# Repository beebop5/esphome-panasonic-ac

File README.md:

# ESPHome Panasonic AC Component (WLAN + CNT)

A custom ESPHome component for controlling Panasonic air conditioning units via UART communication through either:
- **WLAN interface (CN-WLAN port)** (DNSK-P11 compatible)
- **CNT interface (CN-CNT port)** (CZ-TACG1 compatible)

This provides a local-control alternative to Panasonic adapters, without Comfort Cloud.

## Features

* 🌡️ **Climate Control**: Full temperature control with heating, cooling, dry, and fan modes
* 🌪️ **Fan Control**: Automatic and manual fan speed control (1-5 levels)
* 🎛️ **Swing Control**: Independent horizontal and vertical air swing positioning
* ✨ **NanoeX Support**: Control for Panasonic's nanoeX air purification technology
* 📊 **Temperature Monitoring**: Built-in outside temperature sensor support
* 🔄 **Home Assistant Integration**: Seamless integration with Home Assistant's climate platform
* ⚡ **Local Control**: Instant control without cloud delays

## Supported Hardware

### CN-WLAN (DNSK-P11 compatible)

This component works with Panasonic AC units that have a WLAN interface (CN-WLAN port). It serves as a drop-in replacement for the Panasonic DNSK-P11 wireless LAN adapter. Tested as a drop in replacement for part number ACXA73-28520 on:
- CS-RU12YKA
- CS-RU18YKA
- CS-RU24YKA

### CN-CNT (CZ-TACG1 compatible)

This component also supports the **CZ-TACG1 protocol via CN-CNT** (often called “CNT” in configs).

### Requirements

* ESP32 (recommended) or ESP8266
* 5V to 3.3V bi-directional logic level converter (minimum 2 channels)
* Jumper wires for connections
* ESPHome 2025.12.1 or newer (v1.1.0+ requires 2025.12.1+)
* Home Assistant 2024.1.0 or newer

**Note**: Select the protocol with `type:` in the `climate:` config. Default is `wlan`.

## Version History

### v1.1.0 - CN-CNT (CZ-TACG1) Support

**New in v1.1.0:**
- ✨ **CN-CNT protocol support**: Full support for Panasonic AC units with CN-CNT interface (CZ-TACG1 compatible)
- ✨ **Enhanced swing modes**: CNT units support "Auto" and "Swing" modes for vertical swing
- 🔧 **Improved architecture**: Refactored component to support multiple protocol types
- 📚 **Better documentation**: Comprehensive examples for both WLAN and CNT interfaces

See [CHANGELOG.md](CHANGELOG.md) for complete details.

### Breaking Changes in v1.0.0

⚠️ **Version 1.0.0+ requires ESPHome 2025.12.1 or newer** due to API changes in the Climate component.

### What Changed:
- **ESPHome Requirement**: Minimum version increased from 2022.5.0 to **2025.12.1+**
- **Fan Mode & Preset Status**: The climate entity's `custom_fan_mode` and `custom_preset` attributes no longer update automatically from AC telemetry (ESPHome API limitation)

### Migration Guide:
To restore fan mode and preset status reporting, add optional text sensors to your configuration:

```yaml
climate:
  - platform: panasonic_ac
    name: "AC"
    # ... other config ...
    fan_mode_status:
      name: "AC Fan Mode Status"
    preset_status:
      name: "AC Preset Status"
```

These sensors will report the current fan mode (Automatic, 1-5) and preset (Normal, Powerful, Quiet) from AC telemetry.

## Installation

### Software Setup

Add the external component to your ESPHome configuration:

**For stable releases (recommended):**
```yaml
external_components:
  - source:
      type: git
      url: https://github.com/bl0ckstat/esphome-panasonic-ac
      ref: v1.2.1
    components: [panasonic_ac]
```

**For latest development version:**
```yaml
external_components:
  source:
    type: git
    url: https://github.com/bl0ckstat/esphome-panasonic-ac
    ref: master
  components: [panasonic_ac]
```

### Hardware Wiring

> **Purpose-built PCB:** a carrier board for the ESP32-C3 SuperMini that plugs
> into either the CN-WLAN or CN-CNT port lives in [`hardware/`](hardware/) —
> KiCad source, ready-to-order Gerbers, and assembly notes.

Connect your ESP to the AC unit's CN-WLAN port using a logic level converter:

```
ESP32/ESP8266 (3.3V)    Logic Converter    Panasonic AC CN-WLAN (5V)
GPIO17 (TX)         →   TX             →   RX
GPIO16 (RX)         →   RX             →   TX
GND                 →   GND            →   GND
3.3V                →   LV             
5V                  →   HV             →   VCC
```

### Safety Warnings

* ⚠️ **Always disconnect mains power** before opening your AC unit
* ⚠️ **Never connect ESP directly to AC** - the AC uses 5V while ESP uses 3.3V
* ⚠️ **Use a proper logic level converter** to prevent damage to your ESP
* ⚠️ **Installation at your own risk** - no responsibility for damage to equipment

## Configuration

### Complete Example Configuration (CN-WLAN)

```yaml
substitutions:
  device_name: bedroom-ac
  device_name_short: bedroom
  wifi_ssid: "YourWiFiSSID"
  wifi_pass: "YourWiFiPassword"
  api_key: "YourAPIKey"
  ota_pw: "YourOTAPassword"

esphome:
  name: $device_name
  comment: $device_name

esp32:
  board: esp32dev
  framework: 
    type: arduino
    
wifi:
  networks:
  - ssid: $wifi_ssid
    password: $wifi_pass

api:
  encryption:
    key: $api_key
  
ota:
  - platform: esphome
    password: $ota_pw

logger:
  level: DEBUG

time:
  - platform: sntp
    id: my_time
    servers:
    - 0.pool.ntp.org
    - 1.pool.ntp.org

# UART connection to AC unit
uart:
  tx_pin: GPIO17
  rx_pin: GPIO16
  baud_rate: 9600
  parity: EVEN
  rx_buffer_size: 1024

external_components:
  - source:
      type: git
      url: https://github.com/bl0ckstat/esphome-panasonic-ac
      ref: v1.2.1
    components: [panasonic_ac]

# Select controls for swing positioning
select:
  - platform: template
    name: "Panasonic AC Horizontal Swing"
    id: panasonic_ac_hswing
    options:
      - "Left"
      - "Centre Left"
      - "Centre"
      - "Centre Right"
      - "Right"
    initial_option: "Centre"
    optimistic: true

  - platform: template
    name: "Panasonic AC Vertical Swing"
    id: panasonic_ac_vswing
    options:
      - "Up"
      - "Mid Up"
      - "Mid"
      - "Mid Down"
      - "Down"
    initial_option: "Mid"
    optimistic: true

# Optional switches for AC features
switch:
  - platform: restart
    name: "Restart"
  - platform: template
    name: "Panasonic AC NanoeX"
    id: panasonic_ac_nanoex
    restore_mode: RESTORE_DEFAULT_OFF
    optimistic: true
  - platform: template
    name: "Panasonic AC Powerful"
    id: panasonic_ac_powerful
    restore_mode: RESTORE_DEFAULT_OFF
    optimistic: true
  - platform: template
    name: "Panasonic AC Quiet"
    id: panasonic_ac_quiet
    restore_mode: RESTORE_DEFAULT_OFF
    optimistic: true

# Climate component with all features
climate:
  - platform: panasonic_ac
    type: wlan
    name: $device_name_short
    outside_temperature:
      name: "Outside Temperature"
    horizontal_swing_select_id: panasonic_ac_hswing
    vertical_swing_select_id: panasonic_ac_vswing
    nanoex_switch_id: panasonic_ac_nanoex
    powerful_switch_id: panasonic_ac_powerful
    quiet_switch_id: panasonic_ac_quiet
    fan_mode_status:
      name: "AC Fan Mode Status"
    preset_status:
      name: "AC Preset Status"

### Minimal Example (CN-CNT / CZ-TACG1)

For CN-CNT, set `type: cnt`. (Select/switch IDs are optional, but recommended.)

```yaml
climate:
  - platform: panasonic_ac
    type: cnt
    name: "Office AC"
    # Optional wiring-dependent entities:
    # vertical_swing_select_id: my_vswing
    # horizontal_swing_select_id: my_hswing
    # nanoex_switch_id: my_nanoex
    # powerful_switch_id: my_powerful
    # quiet_switch_id: my_quiet
```

CNT swing select options match the WLAN spelling/capitalization:
- Vertical: `Up`, `Mid Up`, `Mid`, `Mid Down`, `Down`, `Swing`, `Auto`
- Horizontal: `Left`, `Centre Left`, `Centre`, `Centre Right`, `Right`, `Auto`

## Local Development / Testing

ESPHome 2026.x requires **Python 3.11+**. To run the same compile locally:

```bash
cd beebop-panasonic-ac
/usr/local/bin/python3.11 -m venv .venv
. .venv/bin/activate
python -m pip install -U pip
python -m pip install esphome==2026.1.0
./scripts/compile_all.sh
```

## Configuration Options

### Climate Component

| Option | Type | Required | Description |
|--------|------|----------|-------------|
| `name` | string | **Yes** | The name for the climate device |
| `type` | string | No | Protocol type: `wlan` (default, DNSK-P11) or `cnt` (CZ-TACG1) |
| `outside_temperature` | sensor | No | Temperature sensor for outside temperature monitoring |
| `horizontal_swing_select_id` | ID | No | ID of template select for horizontal swing control |
| `vertical_swing_select_id` | ID | No | ID of template select for vertical swing control |
| `nanoex_switch_id` | ID | No | ID of template switch for nanoeX control |
| `powerful_switch_id` | ID | No | ID of template switch for Powerful mode control |
| `quiet_switch_id` | ID | No | ID of template switch for Quiet mode control |
| `fan_mode_status` | text_sensor | No | Text sensor to report current fan mode from AC telemetry |
| `preset_status` | text_sensor | No | Text sensor to report current preset from AC telemetry |

### UART Configuration

| Option | Value | Description |
|--------|-------|-------------|
| `tx_pin` | GPIO pin | Transmit pin (typically GPIO17) |
| `rx_pin` | GPIO pin | Receive pin (typically GPIO16) |
| `baud_rate` | 9600 | Communication speed |
| `parity` | EVEN | Required for Panasonic AC communication |

## License

This project is licensed under the MIT License - see the [LICENSE](LICENSE) file for details.

## Acknowledgments

- Based on reverse engineering of Panasonic AC communication protocols
- Built for the ESPHome ecosystem
- Community contributions and testing
- Related work: [DomiStyle/esphome-panasonic-ac](https://github.com/DomiStyle/esphome-panasonic-ac) - A popular ESPHome Panasonic AC component for CN-CNT port interface

## Support

- **Issues**: [GitHub Issues](https://github.com/bl0ckstat/esphome-panasonic-ac/issues)
- **Documentation**: [Component Documentation](https://github.com/bl0ckstat/esphome-panasonic-ac)
- **ESPHome**: [ESPHome Documentation](https://esphome.io/)

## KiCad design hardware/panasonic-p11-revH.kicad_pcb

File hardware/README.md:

# Panasonic AC Interface Board (rev H)

Carrier PCB for this ESPHome component: an ESP32-C3 SuperMini plus a BSS138
level-converter module, connecting to a Panasonic AC through **either** the
CN-WLAN (DNSK-P11) port or the CN-CNT (CZ-TACG1) port.

## Specs

| | |
|---|---|
| Size | 50.5 × 18.0 mm, 1.6 mm FR-4, 2 layers |
| MCU | ESP32-C3 SuperMini (soldered, USB-C at the board edge) |
| Level shifter | BSS138 2-channel module, 10.16 mm row spacing |
| D1 | 1N5819 Schottky (reverse protection + blocks USB 5 V back-feed into the AC) |
| C1 | 100 µF / 16 V radial, 2.0 mm pitch |
| UART | 9600 8E1 — TX = GPIO3, RX = GPIO4 |

## Connectors — fit ONE of J11 / CNT

| Ref | Port | Pinout |
|---|---|---|
| **J11** | CN-WLAN (DNSK-P11), 1.27 mm single-row right-angle, 8-pin | 1 = +5V · 2 = TX (from AC) · 3 = RX (to AC) · 4–7 = NC · 8 = GND |
| **CNT** | CN-CNT (CZ-TACG1), 5-pin 2.54 mm header (pigtail to the AC's JST-PA) | 1 = +5V · 2 = TX · 3 = RX · **4 = +12 V — NO CONNECT (isolated pad)** · 5 = GND |

Both connectors share the same nets; the component's `type: wlan` / `type: cnt`
setting selects the protocol.

> **Warning:** CN-CNT pin 4 carries +12 V from the AC. The pad is intentionally
> connected to nothing. Never bridge it.

## Expansion headers

| Ref | Pins | Level | Notes |
|---|---|---|---|
| **J1** (top edge, 2.54 mm) | IO1 · IO0 · GND · 3V3 | 3.3 V | Direct GPIO, bidirectional |
| **J2** (bottom edge, 2.54 mm) | IO10 · IO7 · GND · 5V | 5 V | Via the BSS138 module's divider channels — **input to the ESP only** (5 V → 3.3 V, unidirectional) |

## Board features

- 3 mm-deep notch at the connector edge: the J11 right-angle pins cantilever
  over it so the AC connector body drops through the board plane.
- Antenna keep-out (no pour/vias) at the ESP32 antenna end; expect to set
  `output_power: 8.5dB` in ESPHome regardless.
- Two 2.5 mm non-plated cable-tie holes flanking the notch for strain relief.
- Ground pour both sides, stitched; all through-hole for hand assembly.

## Ordering

Upload `panasonic-p11-revH-gerbers-pcbway.zip` to PCBWay. Parameters:
2 layers, 50.5 × 18 mm, **1.6 mm** FR-4 TG150, 1 oz, lead-free HASL (or ENIG),
green mask, white silk both sides. `gerbers/README.txt` (included in the zip)
flags the notch and chamfers as intentional so CAM does not query them.

## Files

- `panasonic-p11-revH.kicad_pcb` / `.kicad_pro` — KiCad 9 source (routed, DRC-clean)
- `gerbers/` — plotted fab outputs + fab notes
- `panasonic-p11-revH-gerbers-pcbway.zip` — ready-to-upload fab package
- `generate_placement.py` — regenerates the pre-route placement from code
- `check_silkscreen.py` — verifies silk text is on-board, non-overlapping, off-pad
- `board-front.svg` / `board-back.svg` — renders

## Shopping list (AliExpress)

Search links — many equivalent listings exist; check each against the notes.

| Part | Link | Notes |
|---|---|---|
| ESP32-C3 SuperMini | [search](https://www.aliexpress.com/w/wholesale-esp32-c3-supermini.html) | 22.5 × 18 mm board with USB-C |
| BSS138 level shifter, 2-ch | [search](https://www.aliexpress.com/w/wholesale-2-channel-logic-level-converter-bss138.html) | 2 rows of 6 pins, **10.16 mm row spacing**. Avoid variants with an onboard 3.3 V LDO (see Assembly notes) |
| 1N5819 diode, DO-41 | [search](https://www.aliexpress.com/w/wholesale-1n5819-do-41.html) | 1N4001 also works (more voltage drop) |
| 100 µF / 16 V radial cap | [search](https://www.aliexpress.com/w/wholesale-100uf-16v-electrolytic-capacitor-5mm.html) | 5 mm dia, 2.0 mm lead pitch; body lies flat on the board |
| 1.27 mm right-angle header (J11) | [search](https://www.aliexpress.com/w/wholesale-1.27mm-pitch-right-angle-pin-header.html) | Single row of 8; sold as 2×8 breakaway strips |
| 2.54 mm pin headers (J1/J2/CNT) | [search](https://www.aliexpress.com/w/wholesale-2.54mm-pin-header-single-row.html) | Standard 0.1″ strips |
| JST PA 5-pin pigtail (CNT cable) | [search](https://www.aliexpress.com/w/wholesale-jst-pa-2.0mm-5-pin-cable.html) | Only for the CN-CNT variant; leave the +12 V wire unconnected |
| 30 mm 2:1 heat shrink | [search](https://www.aliexpress.com/w/wholesale-30mm-heat-shrink-tubing.html) | ~70 mm per board, if sealing the assembly |

## Assembly notes

1. Flash the ESP32 over USB-C **before** fitting it if you plan to heat-shrink
   the assembly; verify OTA works before sealing.
2. Check the delivered BSS138 module: if it has an onboard 3.3 V LDO, do not
   feed `LV` from the ESP's 3V3 (see the AliExpress listing warning in the
   project docs).
3. Verify J11 pin 1 (+5 V) against your unit with a meter before first power-up.
4. Trim all leads flush on the back — the board sits against the AC control board.

Isolate mains at the breaker before opening the AC unit.

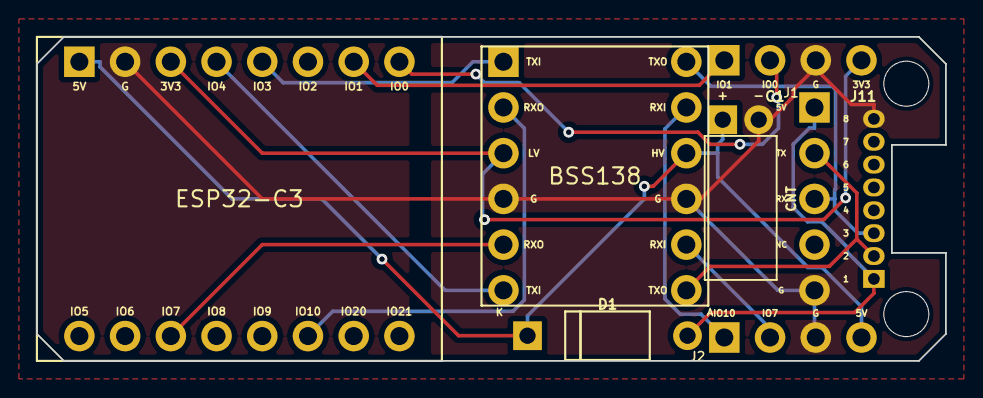
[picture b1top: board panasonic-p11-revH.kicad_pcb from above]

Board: 2 copper layers, 50.5 x 18.0 mm, 10 parts (0 on the bottom side), 14 nets.

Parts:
BSS138: BSS138-2ch-module; U2
C1: 100uF_16V; C1
CNT: CN-CNT_5p_2.54; CNT
D1: 1N5819_DO41; D1
ESP32-C3: ESP32-C3-SuperMini; U1
H1: tie; H1
H2: tie; H2
J1: 1x4; J1
J2: 1x4; J2
J11: 1.27_RA_8way; J11

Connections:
+3V3: BSS138.L3, ESP32-C3.3, J1.4
+5V: BSS138.H3, C1.1, D1.1, ESP32-C3.1, J2.4
AC_5V: CNT.1, D1.2, J11.1
AC_RX_5V: BSS138.H1, CNT.3, J11.3
AC_TX_5V: BSS138.H6, CNT.2, J11.2
ESP_RX: BSS138.L6, ESP32-C3.4
ESP_TX: BSS138.L1, ESP32-C3.5
GND: BSS138.H4, BSS138.L4, C1.2, CNT.5, ESP32-C3.2, J1.3, J2.3, J11.8
IO0: ESP32-C3.8, J1.2
IO1: ESP32-C3.7, J1.1
IO7: BSS138.L5, ESP32-C3.11
IO7_5V: BSS138.H5, J2.2
IO10: BSS138.L2, ESP32-C3.14
IO10_5V: BSS138.H2, J2.1

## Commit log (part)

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2025-06-05 Update names
2025-06-14 bug fux
2025-06-18 _SCHEMA fix
2025-06-21 refector for schema change
2025-09-10 Rewrite README and update project references
    - Complete rewrite of README.md with modern formatting and comprehensive documentation
    - Add proper project description, features, and installation instructions
    - Include safety warnings and troubleshooting section
    - Update LICENSE to include Duncan as copyright holder (2025)
    - Update example config to reference beebop5/esphome-panasonic-ac repository
    - Improve documentation structure with clear sections and emojis
2025-09-10 Update test3 with comprehensive changes
    - Remove CNT interface support (files and code)
    - Rename files for better clarity:
    * esppac.h/cpp → panasonic_ac_base.h/cpp
    * esppac_commands_wlan.h → panasonic_ac_wlan_commands.h
    * ac.yaml.example → panasonic_ac_wlan.yaml.example
    * README.DNSKP11.md → README.WLAN_INSTALLATION.md
2025-09-10 Remove unused method implementations
    - Remove update_eco, update_econavi, update_mild_dry, update_current_power_consumption from base class
    - Remove set_eco_switch, set_econavi_switch, set_mild_dry_switch, set_current_power_consumption_sensor from base class
    - Remove set_current_temperature_sensor method (unused in WLAN-only implementation)
    - Remove on_eco_change, on_econavi_change, on_mild_dry_change from WLAN class
    - Fixes compilation errors from missing method declarations
2025-09-10 Fix ESPHome compilation command syntax
    - Remove deprecated --board flag from esphome compile commands
    - Use board configuration from YAML file instead
    - Create temporary ESP8266 config for testing
    - Fixes GitHub Actions test failures
2025-09-10 Fix select and switch component schema registration
    - Remove explicit ID declaration for select and switch components
    - Use standard SELECT_SCHEMA and SWITCH_SCHEMA without custom ID generation
    - This prevents ESPHome from trying to instantiate abstract base classes
    - The new_select and new_switch functions handle proper component creation
2025-09-10 Try using proper Select class for select components
    - Import Select class from esphome.components.select
    - Use Select class instead of select.Select in schema declarations
    - This should resolve the abstract class instantiation issue
2025-09-10 Try manual select component creation
    - Remove ID generation from schema to avoid abstract class issues
    - Create select components manually using cg.new_Pvariable
    - Set name and options manually instead of using select.new_select
    - This should bypass the problematic select component registration
2025-09-10 Fix select component creation using ESPHome's built-in pattern
    - Use select.SELECT_SCHEMA.extend() instead of manual ID declaration
    - Use select.new_select() instead of manually creating Select instances
    - Remove direct Select import since we use ESPHome's built-in functions
    - This should resolve the abstract class instantiation errors
2025-09-10 Fix component registration by adding proper __init__.py
    - Add proper imports and exports in __init__.py to register the component
    - This should resolve 'Platform not found: climate.panasonic_ac' error
    - ESPHome needs __init__.py to properly discover and load external components
2025-09-10 Fix switch component abstract class instantiation
    - Remove switch.SWITCH_SCHEMA to avoid abstract class instantiation
    - Temporarily disable switch component creation in to_code function
    - Remove switch component from test configuration
    - Component is now compiling successfully, just need to handle switch components properly
2025-09-11 Update test config to use master branch
2025-09-11 Implement command queuing to prevent UART blocking during handshake
    - Add command queue system to batch UART operations
    - Queue commands instead of sending immediately to avoid blocking
    - Process one command per loop iteration with 5ms minimum interval
    - Prevents multiple rapid UART writes during handshake sequence
    - Addresses: 'panasonic_ac.climate took a long time for an operation (57 ms)'
    - Maintains full functionality while eliminating performance warnings
2025-09-11 Fix handshake initialization timing by using direct packet sending
    - Use direct send_packet() for handshake 1 and 2 instead of queued send_command()
    - Prevents timing issues during critical handshake initialization phase
    - Ensures handshake packets are sent immediately without queuing delays
    - Fixes: Component getting stuck after handshake 2 response
    - Maintains command queuing for regular handshake responses (3-16)
2025-09-11 Add debug logging to handshake staged processing
    - Add debug logs to track handshake packet identification stages
    - Log when handshake packet identification starts
    - Log when specific handshake response types are identified
    - Log when moving to responding stage with handshake type
    - Helps diagnose why handshake processing gets stuck after receiving response
2025-09-11 Add debug logging for unknown handshake packets
    - Log unknown handshake packet bytes when they don't match expected patterns
    - Helps diagnose what packets are being received after handshake 13
    - Will show if AC is sending unexpected packet formats for handshake 14/15
2025-09-23 Remove WLAN references and rename files
    - Renamed panasonic_ac_wlan.yaml.example to panasonic_ac.yaml.example
    - Renamed README.WLAN_INSTALLATION.md to README.INSTALLATION.md
    - Updated all references from 'WLAN' to 'CN' in documentation
    - Updated code comments from 'CN-WLAN' to 'CN'
    - Updated README.md to reference new file names and terminology
    - Updated test_component.sh to reference new file names
2025-09-23 Fix horizontal_swing_select and vertical_swing_select configuration options
    - Added missing configuration schema for horizontal_swing_select and vertical_swing_select
    - Added missing configuration schema for nanoex_switch
    - Implemented template select and switch component creation in to_code function
    - Users can now use these options directly in climate configuration
    - All configurations now validate successfully
2025-09-23 Fix swing option values to match C++ implementation
    - Updated HORIZONTAL_SWING_OPTIONS to match C++ expected values: Left, Centre Left, Centre, Centre Right, Right
    - Updated VERTICAL_SWING_OPTIONS to match C++ expected values: Up, Mid Up, Mid, Mid Down, Down
    - Added optimistic mode to select components for better responsiveness
    - Now when users change swing mode, the C++ on_horizontal_swing_change() and on_vertical_swing_change() methods will be called
    - Users should now see debug messages like 'Setting horizontal swing position' when changing swing modes
2025-09-24 Add support for connecting external select/switch components
    - Add CONF_*_ID options to connect external components by ID
    - Update climate.py to support both embedded and external component approaches
    - Test configuration successfully compiles with external template components
    - This resolves the connection issue between template selects and Panasonic AC component
2025-09-24 Add logging for additional poll response fields
    - Added verbose logging for unknown fields 0x20, 0x21, 0x32, 0x34, 0x35, 0xBB, 0xBE
    - These fields are requested in the poll command but not currently processed
    - Will help identify if these fields contain useful information like additional sensors or status indicators
    - Requires verbose logging level to see the values
2025-09-24 Fix outside temperature sensor state comparison
    - Fixed sensor state comparison by casting temperature to float for proper type matching
    - Added debug logging to show received temperature and current sensor state
    - Resolves issue where outside temperature sensor stopped updating due to type mismatch
    - Should restore outside temperature functionality that was broken ~1 hour ago
2025-09-24 Initial commit: ESPHome Panasonic AC component
    - Clean ESPHome component for Panasonic AC control
    - Supports external select/switch components for swing and nanoeX control
    - Includes example configurations and test setup
    - Optimized climate.py without superfluous internal component creation code
2025-09-25 Clean up panasonic_ac_base.cpp
    - Remove commented-out code and improve formatting
    - Consolidate temperature validation logic into is_valid_temperature() helper function
    - Reduce code duplication across temperature update functions
    - Remove excessive blank lines and improve code organization
    - Enhance comments and documentation for better readability
    - Maintain full functionality - all tests pass
2025-09-27 Update documentation to highlight DNSK-P11 replacement capability
    - Add DNSK-P11 replacement information to main description
    - Add dedicated section explaining replacement for ACXA73-28520 part number
    - Highlight enhanced features compared to original DNSK-P11 adapter
    - Add DNSK-P11 replacement as first feature in features list
    - Emphasize local control and open source benefits
2025-10-01 Update component name and documentation to reflect WLAN interface focus
    - Change component name from 'Panasonic AC' to 'Panasonic AC WLAN' in manifest
    - Update README title to 'ESPHome Panasonic AC WLAN Component'
    - Clarify that this component is specifically for CN-WLAN port interface
    - Add note distinguishing from CN-CNT port interface (DomiStyle component)
    - Update wiring diagram to specify CN-WLAN port connection
    - Emphasize DNSK-P11 replacement functionality via WLAN interface
2025-10-01 Replace panasonic_ac.yaml.example with panasonic_ac.yaml
    - Remove example file and add actual configuration file
    - Maintain same comprehensive production-style configuration
    - Keep all realistic features and security settings
2025-10-08 Fix critical bugs and add Powerful/Quiet switches
    CRITICAL BUG FIXES:
    - Fix header validation to accept both 0x5A and 0x3A headers (AC uses 0x3A for responses!)
    - This was causing ALL temperature readings and state updates to be dropped
    - Fix query response size check (was too strict at 125 bytes, now accepts 140+ bytes)
    - Add support for 0x90 response packet variants (poll responses, ACKs, reports)
    NEW FEATURES:
2025-10-09 Add enhanced telemetry packet decoding
    - Remove duplicate RX packet logging in handle_handshake_packet()
    - Decode telemetry packet structure (0x11 0x03)
    - Identify state change flag at byte 7 (0x01 when state changes)
    - Parse power state from data blocks at bytes 50, 90, 130
    - Extract temperature readings from 4 data blocks
    - Add diagnostic logging when AC is running
2025-10-09 Correct telemetry temperature mapping based on actual data
    Analysis of real telemetry data showed:
    - Position 16: 0x1B (27°C) - Outdoor temperature
    - Position 57: 0x1B (27°C) - Outdoor temperature duplicate
    - Position 58: 0x16 (22°C) - Indoor/room temperature
    - Position 59: 0x15 (21°C) - Target temperature
    - Position 56: 0xFD - Status byte (not temperature)
2025-12-23 Fix compilation errors for ESPHome 2025.8.3
    - Fix ClimateCall API usage: use != nullptr instead of .has_value() for custom_fan_mode and custom_preset
    - Fix field assignments: use custom_fan_mode_ and custom_preset_ (with underscore) to match Climate base class
    - Fix return types: change determine_fan_speed() and determine_preset() to return const char* instead of std::string
    - Fix fan mode consistency: change 'Auto' to 'Automatic' to match traits declaration
    Tested and verified compilation with ESPHome 2025.8.3
2025-12-23 Bump version to 1.0.0 and update documentation for breaking changes
    - Update version to 1.0.0 (major version bump for breaking changes)
    - Update ESPHome requirement to 2025.12.1+
    - Add breaking changes section to README with migration guide
    - Document new optional text sensors for status reporting
2025-12-23 Add text_sensor to AUTO_LOAD for component dependencies
    - Fixes compilation error: text_sensor header not found
    - Required because we use text_sensor components for status reporting
2025-12-23 Update README.md for Panasonic AC component configuration
    - Refactor external component configuration to specify Git source with version reference for stable and development releases.
    - Add new optional text sensors: fan_mode_status and preset_status for reporting current AC state.
    - Enhance documentation to clarify configuration options for new text sensors.
2026-01-21 Use simple type selector for WLAN vs CNT
2026-01-21 Improve CNT logging to match WLAN verbosity
